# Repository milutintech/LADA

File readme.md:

# LADA
## Interieur
### Mittelkonsole  Kosten ca 500.-
Open Auto Pro
- Waveshare display 
  - https://www.waveshare.com/product/raspberry-pi/displays/lcd-oled/15.6hp-capqled.htm
- PI 4
  - https://www.pi-shop.ch/raspberry-pi-4-model-b-8gb
- CPC200-CCPA (Car Play)
  - https://www.mytrendyphone.ch/shop/carlinkit-cpc200-ccpa-drahtlose-carplay-android-auto-adapter-304415p.html?gclid=CjwKCAiA3aeqBhBzEiwAxFiOBi3R6-FiMQM87529C-vewYi9WbjxqfM-s6FcQSQeUMXNf6h3jQiDPxoCrb8QAvD_BwE
- CSR8510 A10 (Bt)
  -https://www.digitec.ch/de/s1/product/tp-link-ub500-sender-bluetooth-audio-adapter-16644981
- HIFI BERRY
  -https://www.reichelt.com/ch/de/raspberry-pi-shield-beocreate-4-channel-amplifier-rpi-hb-beocreate-p218586.html?PROVID=2808&gclid=CjwKCAiA3aeqBhBzEiwAxFiOBsO-QmUIh61FRokT5aY90-eXIpBP11wS4Q5fO7jmrViyCtoBBXhQuxoC0AgQAvD_BwE
  
### Tacho
Digifitz

## BMS Kosten ca 2700.-
Orion 
### Ansteuerung

### Verkabelung

https://www.orionbms.com/manuals/pdf/orionbms2_wiring_manual.pdf

> - If fewer than 12 cells are populated in a group, unused cell taps must all be connected to the highest
potential cell in that group. For example, if 6 cells are populated in a group, taps 6 – 12 all must be
connected to the positive tap on cell 6.*

> - No cell group may have fewer than 4 cells connected (higher minimums may apply if a cell's
minimum voltage is below 2.8v). If a group of cells ends up with fewer than 4 cells, some cells must
be skipped in one of the other groups and wired into the group with less than 4 to ensure that a
minimum of 4 cells are present.

> - Cell Groups must have a minimum normal working voltage of 11 volts (2.8v per cell for 4 cells) and
an absolute minimum voltage of 10v. Accuracy of voltage measurements is decreased when the
group voltage is below 11 volts.

> - If a cell group has 0 cells connected (the group is skipped entirely), all wires from that group may be
left disconnected.

### Lade und Ready Modi

The BMS has two primary modes of operation: Charge Mode and Ready Mode. The BMS will enter into Charge Mode any time 12 - 24v is applied to the CHARGE power pin (Main I/O pin 3), regardlessof whether READY power is also present or not.

https://www.orionbms.com/manuals/pdf/orionbms2_operational_manual.pdf

> The following functions are enabled (or change) when the BMS is in Charge Mode:
> 1. The charger safety output is allowed to turn on if enabled and if all criteria have been met.
> 2. The BMS will cap the state of charge to the value specified as the "Charged SOC" percentage.
Even if the battery is charged in such a way that would normally cause the SOC to rise above
this value, the value will not exceed the "Charged SOC parameter" while the BMS is in charge
mode.

> 4. When any cell voltage hits the maximum cell voltage (resulting in the BMS turning the charger
off), the BMS will immediately adjust the state of charge to the "Charged SOC" value since the
BMS knows that the battery pack is fully charged at this time.

> 5. The cell balancing algorithm is enabled and will begin balancing as soon as any cell voltage
goes above the "Start Balancing" voltage. Balancing will continue until all cell voltages are
balanced to within the balance delta voltage parameter. See the “How Balancing Works” section
for more information on cell balancing.

> 6. Certain CANBUS messages may be transmitted or not transmitted depending on whether the
BMS is in CHARGE mode or not (if configured).

> 7. The maximum possible current limit for charging is limited to the "Maximum Amperage While
Charging" parameter available on the “Charge Limits” profile settings tab.
> 8. The maximum allowable cell voltage is limited to the "Max. Voltage While Charging" parameter
available on the “Cell Settings” profile settings tab.

### Flussdiagramme Charge und Discharge

charge

discharge

### Offerte BMS

[S07459.pdf](https://github.com/milutintech/LADA/files/13288886/S07459.pdf)

### NLG

### Relais

## Pinout VCU relais

> - Relais 1 Bat arm
> - Relais 2 KühlPumpe
> - Relais 3 Lüfter
> - Relais 4 NLG KL15
> - Relais 5 Rückfahrlicht
> - Relais 6 DMC KL15
> - Relais 7 BSC KL15

## Pinout Input

> - P1/9 RELAY U2
> - P2/22 IGNITION
> - P3/10 UNLCKCON
> - P4/23
> - A0/7 Gaspedal
> - CAN/25 CAN_H
> - CAN/13 CAN_L

## BMS Messages
Source: BMS
ID 0x1 MSB 00 00 00 00 00 00 00 00 LSB 
> - BMS_SOC 0%-100% byte 0
> - BMS_U_BAT 0V-450V byte 1,2
> - BMS_I_BAT 0A-650A byte 3,4
> - BMS_MAX_Discharge 0A-650A 5,6
> - BMS_MAX_Charge 0A-250A 7

## INFO Messages
Source: INFO
ID 0x3 MSB 00 00 00 00 00 00 00 00 LSB 
> - MAX_CHG_SOC 0%-100% byte 0
> - DMC_TrqRq 0Nm-1100Nm byte 1,2
> - NLG_AcCurrLimMax 0A-32A byte 3
> - OFFROAD_MODE 0-1 byte 4

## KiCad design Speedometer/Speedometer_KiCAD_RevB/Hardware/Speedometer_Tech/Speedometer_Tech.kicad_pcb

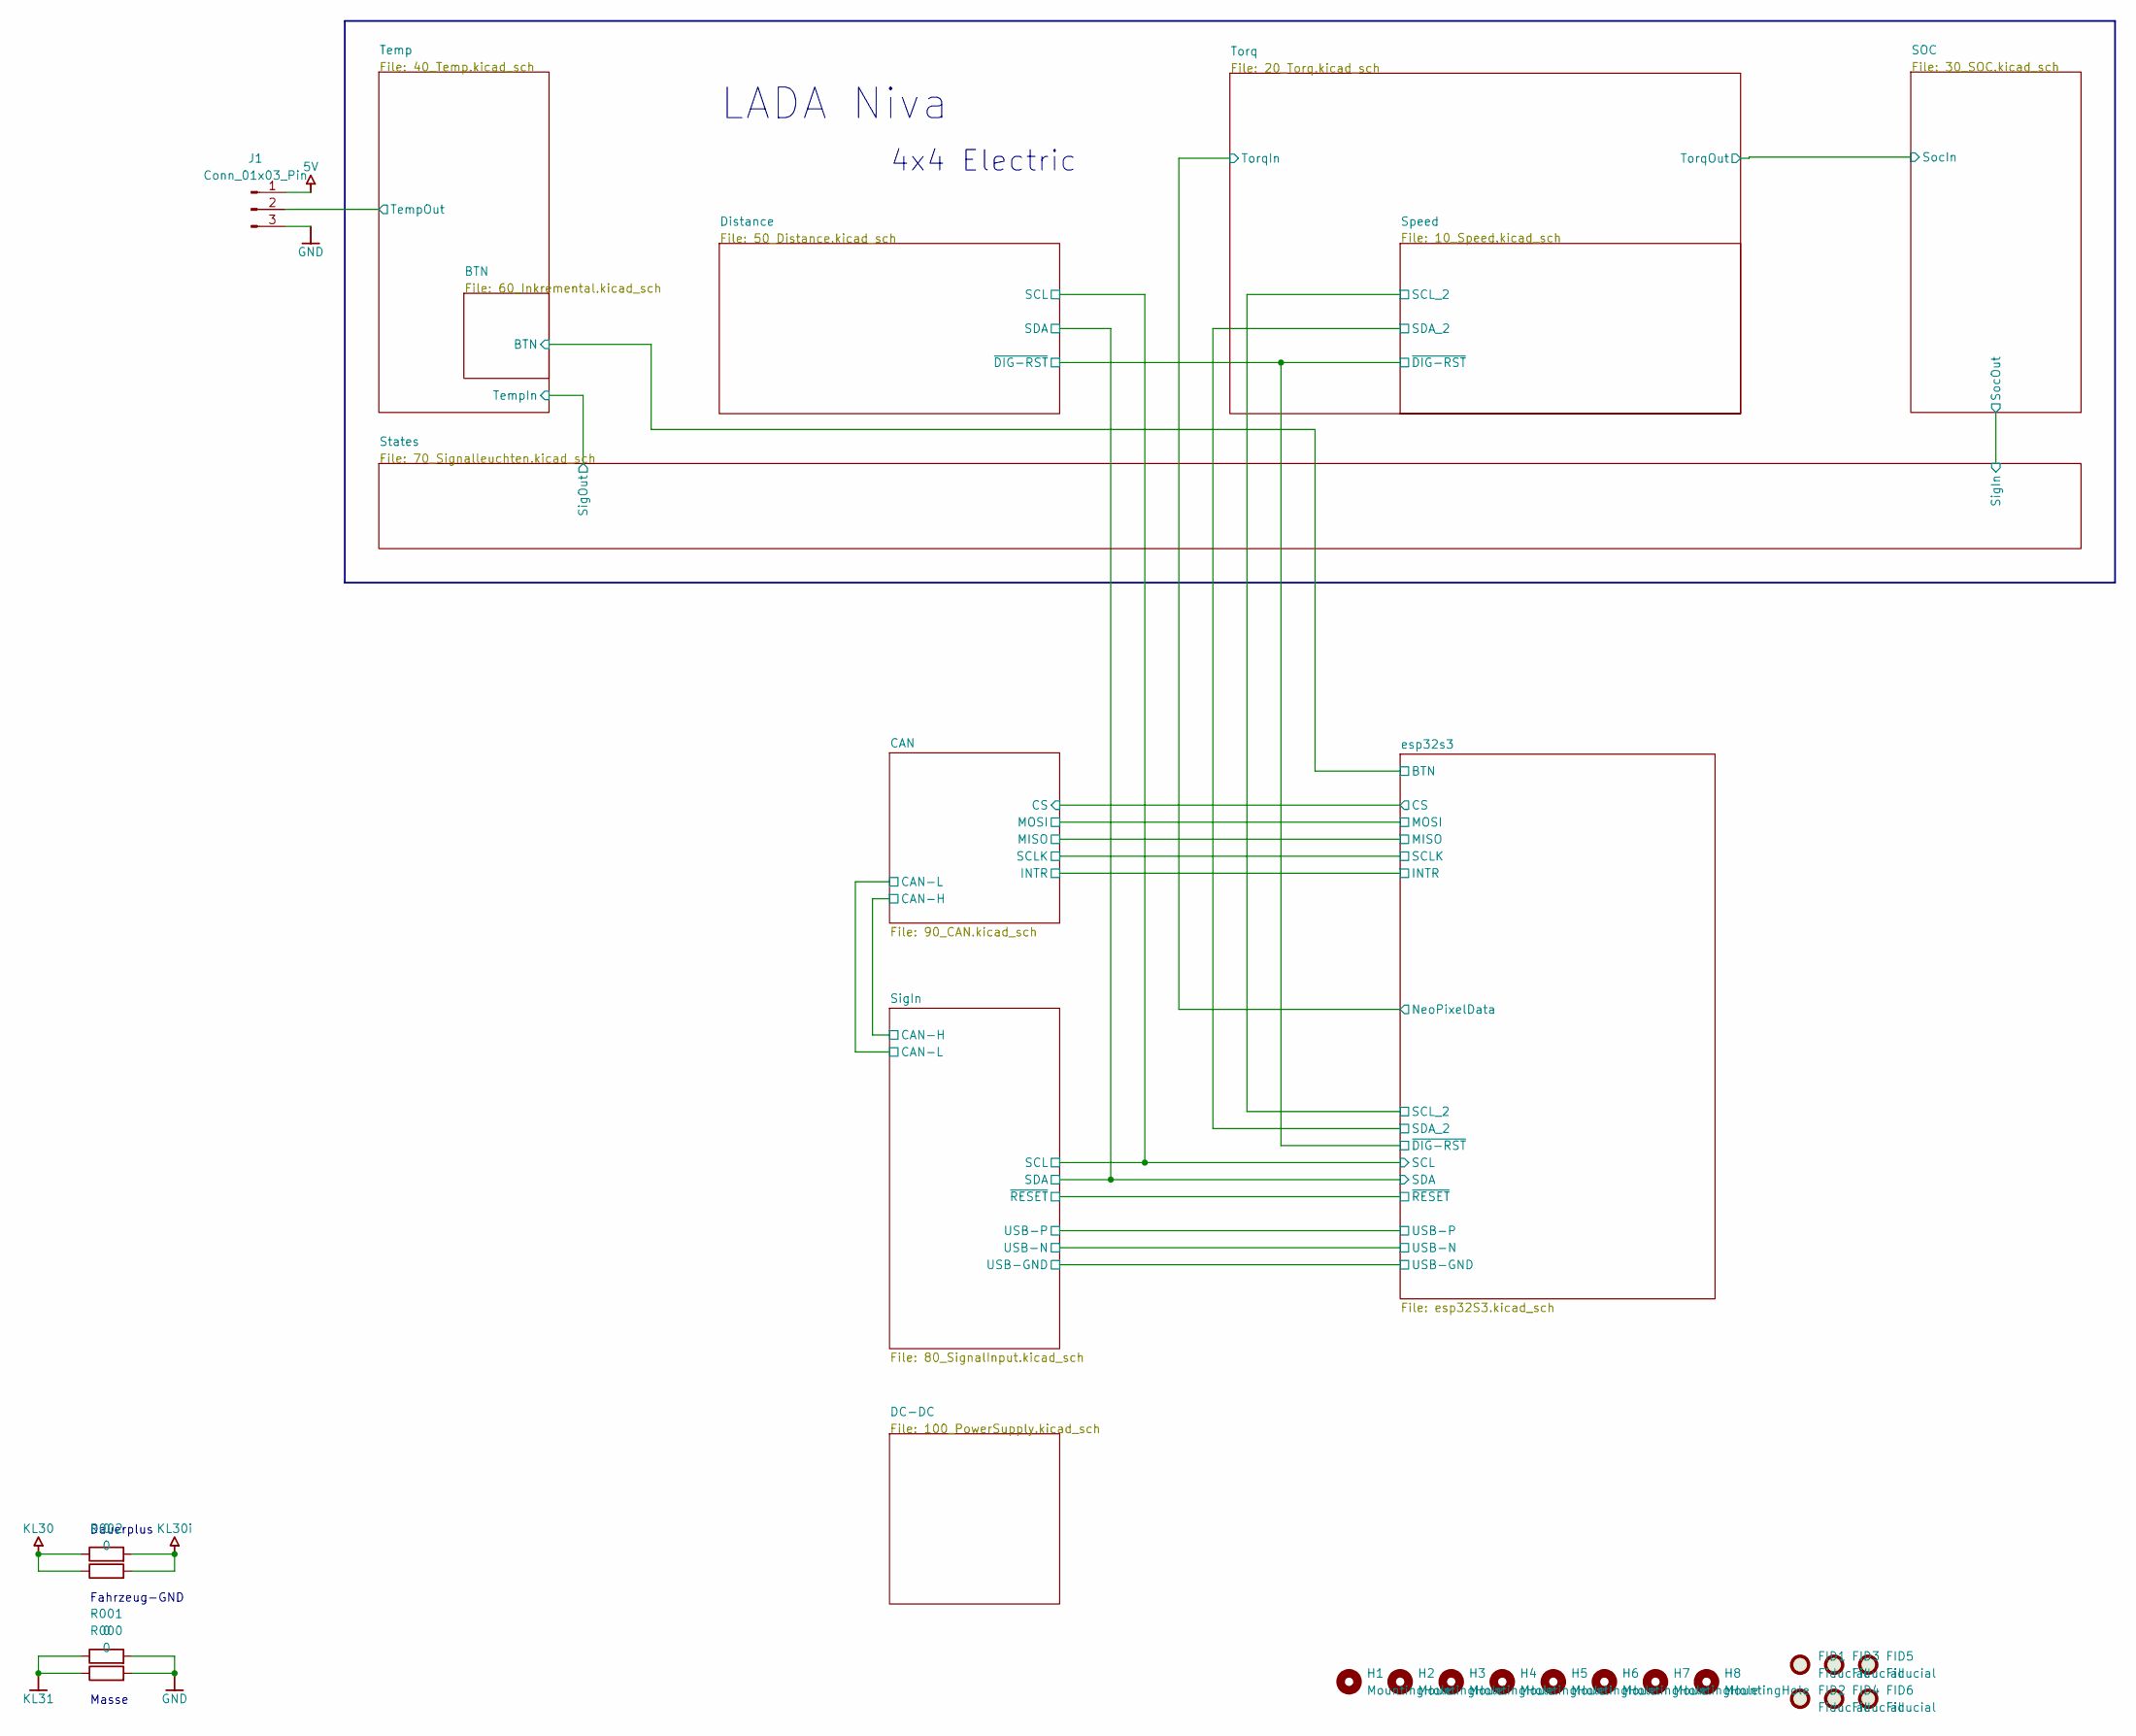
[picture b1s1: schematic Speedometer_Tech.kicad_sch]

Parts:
FID1, FID2, FID3, FID4, FID5, FID6: Fiducial; Fiducial_0.5mm_Mask1mm
H1, H2, H3, H4, H5, H6, H7, H8: MountingHole; MountingHole_4.3mm_M4_ISO7380
J1: Conn_01x03_Pin; PinHeader_1x03_P2.54mm_Horizontal
R000, R001, R002, R003: 0; R_0603_1608Metric

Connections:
5V: J1.1; also elsewhere on the board
/Temp/TempOut: J1.2; also elsewhere on the board
GND: J1.3, R000.2, R001.2; also elsewhere on the board
KL30: R002.1, R003.1; also elsewhere on the board
KL30i: R002.2, R003.2; also elsewhere on the board
KL31: R000.1, R001.1; also elsewhere on the board

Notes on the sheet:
LADA Niva
Masse
4x4 Electric
Dauerplus
Fahrzeug-GND

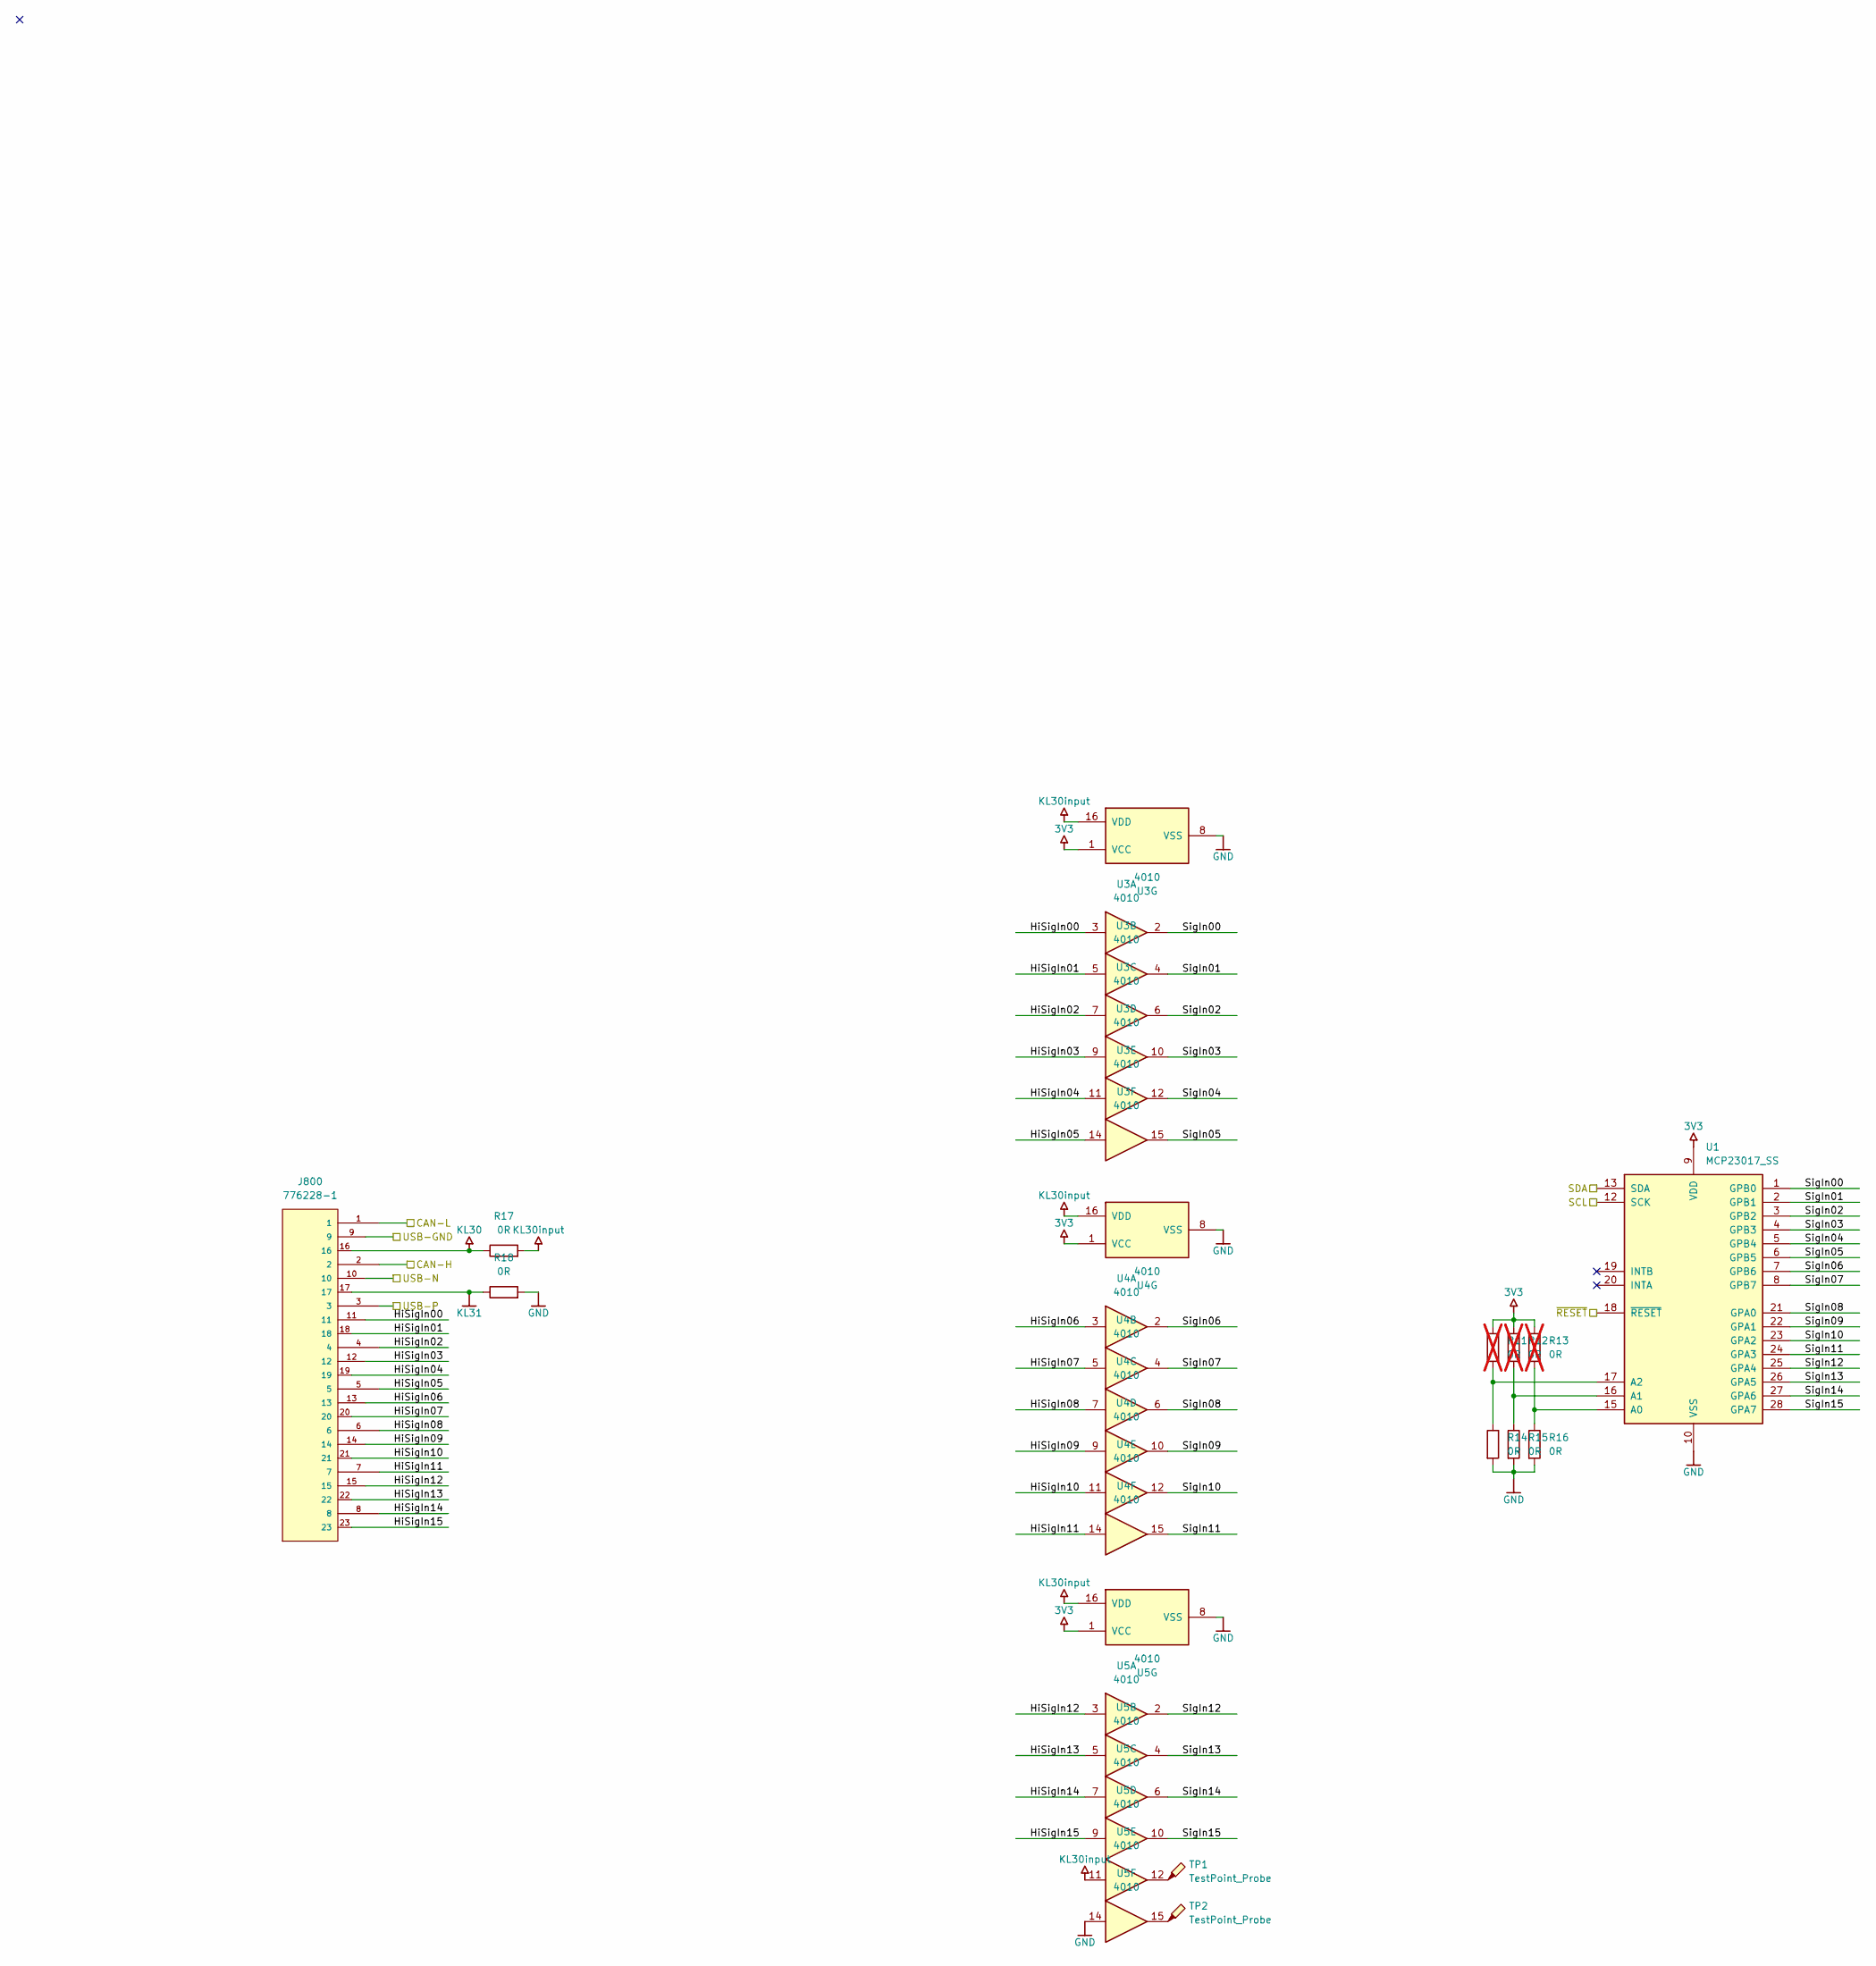
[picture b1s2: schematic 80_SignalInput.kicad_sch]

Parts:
J800: 776228-1; TE_776228-1; PARTREV C13
R11, R12, R13: 0R; R_0603_1608Metric; not fitted
R14, R15, R16, R17, R18: 0R; R_0603_1608Metric
TP1, TP2: TestPoint_Probe; TestPoint_Pad_2.0x2.0mm
U1: MCP23017_SS; SSOP-28_5.3x10.2mm_P0.65mm
U3, U4, U5: 4010; DIP-16_W7.62mm_LongPads

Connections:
3V3: R11.1, R12.1, R13.1, U1.9 (VDD), U3.1 (VCC), U4.1 (VCC), U5.1 (VCC); also elsewhere on the board
/CAN/CAN_H: J800.2; also elsewhere on the board
/CAN/CAN_L: J800.1; also elsewhere on the board
/Distance/SCL: U1.12 (SCK); also elsewhere on the board
/Distance/SDA: U1.13 (SDA); also elsewhere on the board
/SigIn/HiSigIn00: J800.11, U3.3
/SigIn/HiSigIn01: J800.18, U3.5
/SigIn/HiSigIn02: J800.4, U3.7
/SigIn/HiSigIn03: J800.12, U3.9
/SigIn/HiSigIn04: J800.19, U3.11
/SigIn/HiSigIn05: J800.5, U3.14
/SigIn/HiSigIn06: J800.13, U4.3
/SigIn/HiSigIn07: J800.20, U4.5
/SigIn/HiSigIn08: J800.6, U4.7
/SigIn/HiSigIn09: J800.14, U4.9
/SigIn/HiSigIn10: J800.21, U4.11
/SigIn/HiSigIn11: J800.7, U4.14
/SigIn/HiSigIn12: J800.15, U5.3
/SigIn/HiSigIn13: J800.22, U5.5
/SigIn/HiSigIn14: J800.8, U5.7
/SigIn/HiSigIn15: J800.23, U5.9
/SigIn/SigIn00: U1.1 (GPB0), U3.2
/SigIn/SigIn01: U1.2 (GPB1), U3.4
/SigIn/SigIn02: U1.3 (GPB2), U3.6
/SigIn/SigIn03: U1.4 (GPB3), U3.10
/SigIn/SigIn04: U1.5 (GPB4), U3.12
/SigIn/SigIn05: U1.6 (GPB5), U3.15
/SigIn/SigIn06: U1.7 (GPB6), U4.2
/SigIn/SigIn07: U1.8 (GPB7), U4.4
/SigIn/SigIn08: U1.21 (GPA0), U4.6
/SigIn/SigIn09: U1.22 (GPA1), U4.10
/SigIn/SigIn10: U1.23 (GPA2), U4.12
/SigIn/SigIn11: U1.24 (GPA3), U4.15
/SigIn/SigIn12: U1.25 (GPA4), U5.2
/SigIn/SigIn13: U1.26 (GPA5), U5.4
/SigIn/SigIn14: U1.27 (GPA6), U5.6
/SigIn/SigIn15: U1.28 (GPA7), U5.10
/SigIn/USB-N: J800.10; also elsewhere on the board
/SigIn/USB-P: J800.3; also elsewhere on the board
/SigIn/~RESET: U1.18 (~RESET); also elsewhere on the board
GND: J800.9, R14.2, R15.2, R16.2, R18.2, U1.10 (VSS), U3.8 (VSS), U4.8 (VSS), U5.8 (VSS), U5.14; also elsewhere on the board
KL30: J800.16, R17.1; also elsewhere on the board
KL30input: R17.2, U3.16 (VDD), U4.16 (VDD), U5.11, U5.16 (VDD)
KL31: J800.17, R18.1; also elsewhere on the board
unnamed: TP1.1, U5.12
unnamed: TP2.1, U5.15
unnamed: R13.2, R16.1, U1.15 (A0)
unnamed: R12.2, R15.1, U1.16 (A1)
unnamed: R11.2, R14.1, U1.17 (A2)

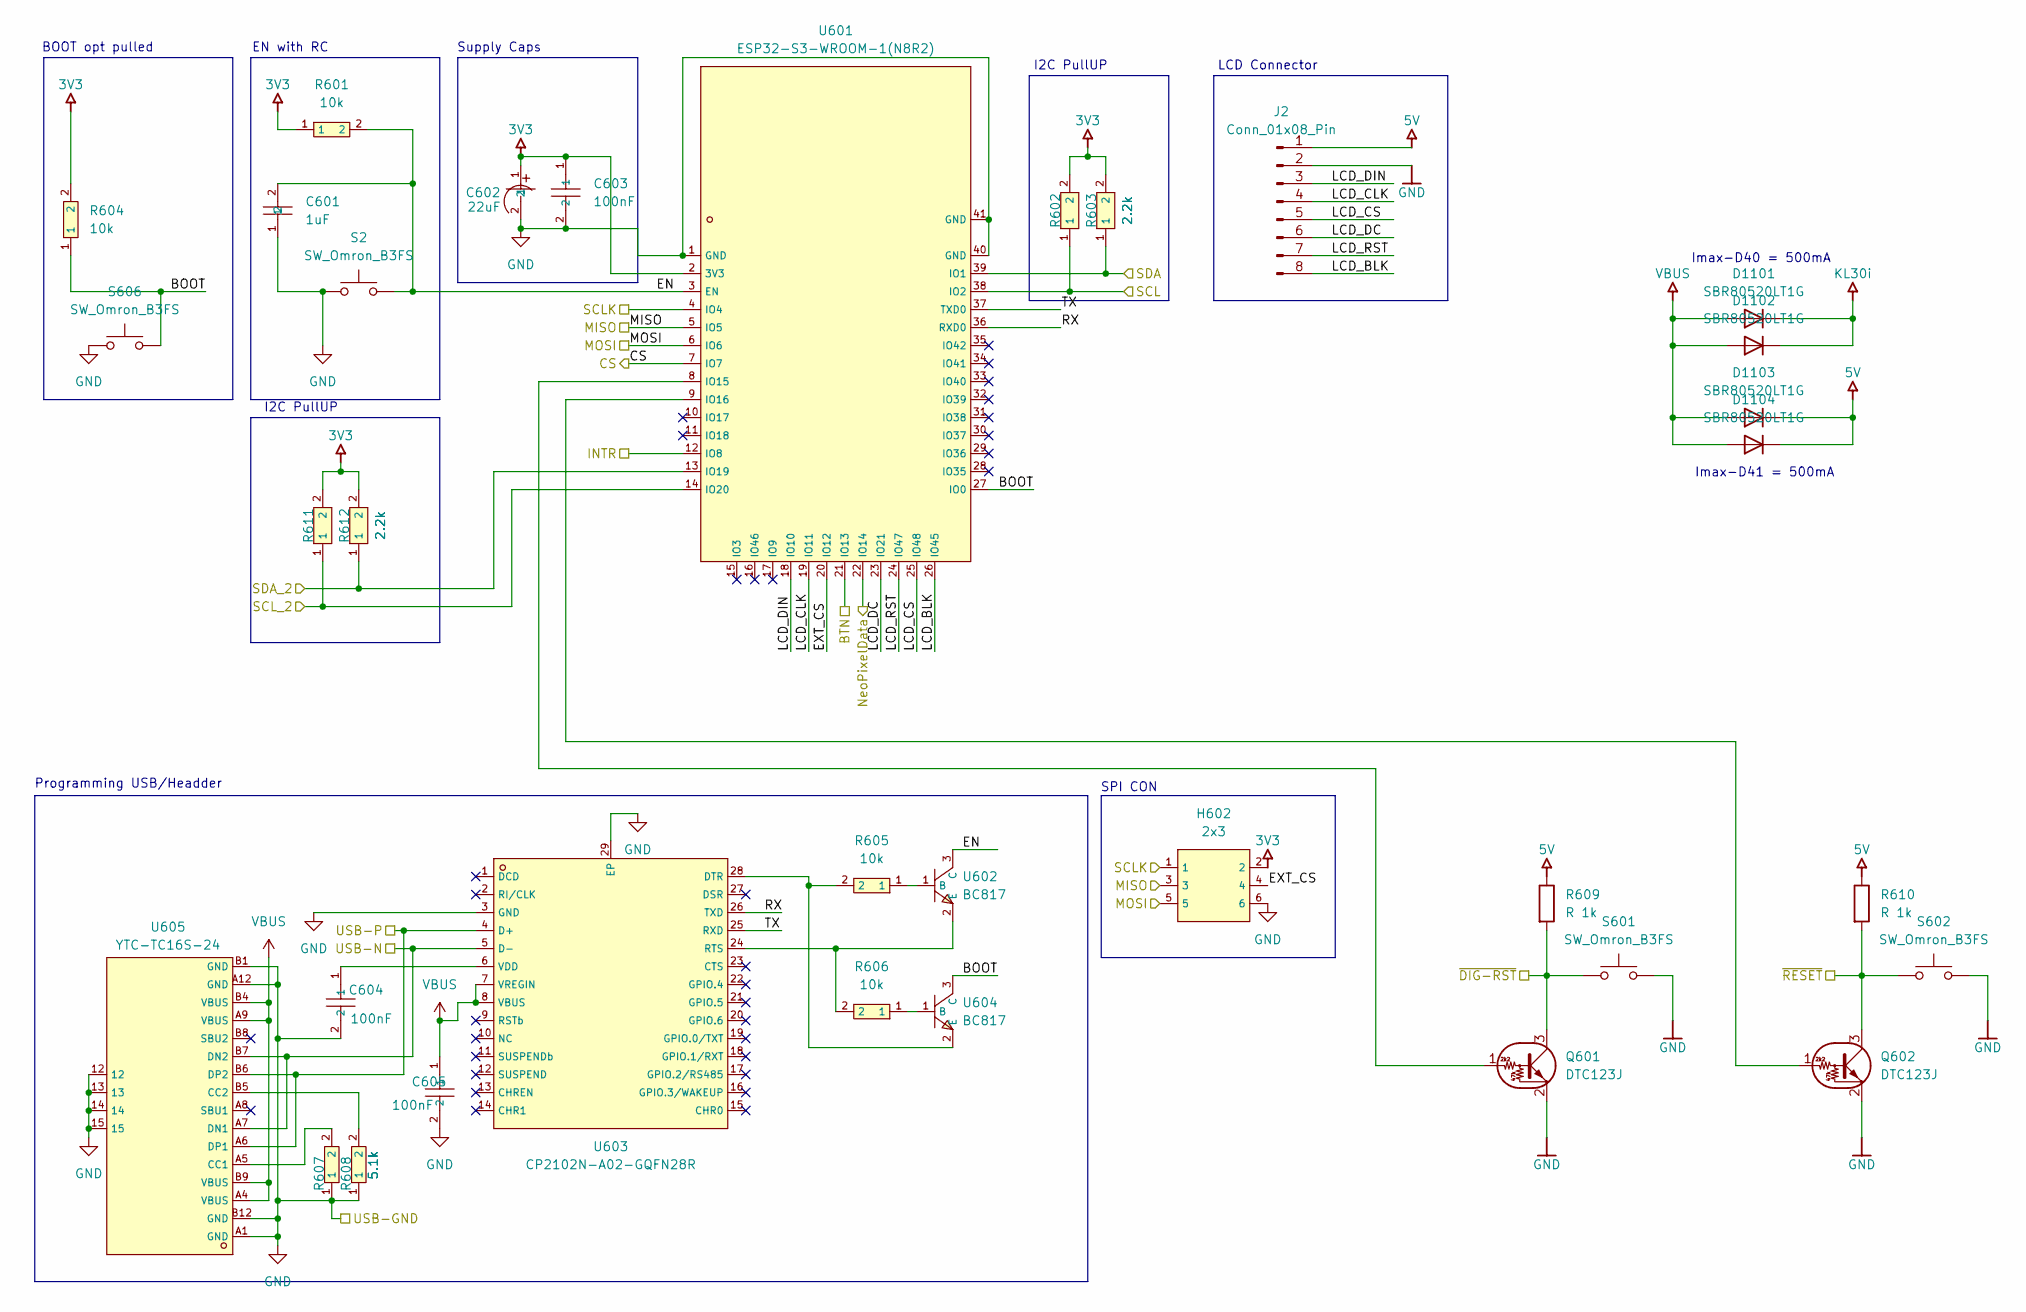
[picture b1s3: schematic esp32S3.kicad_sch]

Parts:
C601: 1uF; C_0805_2012Metric; LCSC C28323
C602: 22uF; C_0805_2012Metric; LCSC C131114
C603: 100nF; C_0201_0603Metric; LCSC C14663
C604: 100nF; C_0603_1608Metric; LCSC C14663
C605: 100nF; R_0603_1608Metric; LCSC C14663
D1101, D1102, D1103, D1104: SBR80520LT1G; D_SOD-123
H602: 2x3; PinHeader_2x03_P2.54mm_Vertical_SMD; LCSC C65114
J2: Conn_01x08_Pin; Harwin_M20-89008xx_1x08_P2.54mm_Horizontal
Q601, Q602: DTC123J; SOT-23
R601, R604, R605, R606: 10k; R_0603_1608Metric; LCSC C98220
R602, R603, R611, R612: 2.2k; R_0603_1608Metric; LCSC C227479
R607, R608: 5.1k; R_0603_1608Metric; LCSC C186203
R609, R610: R 1k; R_0603_1608Metric
S2, S601, S602, S606: SW_Omron_B3FS; SW_SPST_Omron_B3FS-100xP
U601: ESP32-S3-WROOM-1(N8R2); ESP32-S3-WROOM-2; LCSC C2913204
U602, U604: BC817; SOT-23-3; LCSC C549442
U603: CP2102N-A02-GQFN28R; VQFN-28-1EP_5x5mm_P0.5mm_EP3.25x3.25mm; LCSC C964632
U605: YTC-TC16S-24; TYPEC-300D-BCP16H100; LCSC C2927291

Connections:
3V3: C602.1, C603.1, H602.2, R601.1, R602.2, R603.2, R604.2, R611.2, R612.2, U601.2 (3V3); also elsewhere on the board
5V: D1103.1 (K), D1104.1 (K), J2.1, R609.1, R610.1; also elsewhere on the board
/BTN/BTN: U601.21 (IO13); also elsewhere on the board
/CAN/INTR: U601.12 (IO8); also elsewhere on the board
/CAN/SCLK: H602.1, U601.4 (IO4); also elsewhere on the board
/Distance/SCL: R602.1, U601.38 (IO2); also elsewhere on the board
/Distance/SDA: R603.1, U601.39 (IO1); also elsewhere on the board
/Distance/~DIG-RST: Q601.3 (C), R609.2, S601.1; also elsewhere on the board
/SigIn/USB-N: U603.5 (D-), U605.A7 (DN1), U605.B7 (DN2); also elsewhere on the board
/SigIn/USB-P: U603.4 (D+), U605.A6 (DP1), U605.B6 (DP2); also elsewhere on the board
/SigIn/~RESET: Q602.3 (C), R610.2, S602.1; also elsewhere on the board
/Speed/SCL_2: R611.1, U601.14 (IO20); also elsewhere on the board
/Speed/SDA_2: R612.1, U601.13 (IO19); also elsewhere on the board
/Torq/TorqIn: U601.22 (IO14); also elsewhere on the board
/esp32s3/BOOT: R604.1, S606.2, U601.27 (IO0), U604.3 (C)
/esp32s3/CS: U601.7 (IO7); also elsewhere on the board
/esp32s3/EN: C601.2, R601.2, S2.2, U601.3 (EN), U602.3 (C)
/esp32s3/EXT_CS: H602.4, U601.20 (IO12)
/esp32s3/LCD_BLK: J2.8, U601.26 (IO45)
/esp32s3/LCD_CLK: J2.4, U601.19 (IO11)
/esp32s3/LCD_CS: J2.5, U601.25 (IO48)
/esp32s3/LCD_DC: J2.6, U601.23 (IO21)
/esp32s3/LCD_DIN: J2.3, U601.18 (IO10)
/esp32s3/LCD_RST: J2.7, U601.24 (IO47)
/esp32s3/MISO: H602.3, U601.5 (IO5); also elsewhere on the board
/esp32s3/MOSI: H602.5, U601.6 (IO6); also elsewhere on the board
/esp32s3/RX: U601.36 (RXD0), U603.26 (TXD)
/esp32s3/TX: U601.37 (TXD0), U603.25 (RXD)
GND: C601.1, C602.2, C603.2, C604.2, C605.2, H602.6, J2.2, Q601.2 (E), Q602.2 (E), R607.1, R608.1, S2.1, S601.2, S602.2, S606.1, U601.1 (GND), U601.40 (GND), U601.41 (GND), U603.3 (GND), U603.29 (EP), U605.12, U605.13, U605.14, U605.15, U605.A1 (GND), U605.A12 (GND), U605.B1 (GND), U605.B12 (GND); also elsewhere on the board
KL30i: D1101.1 (K), D1102.1 (K); also elsewhere on the board
unnamed: Q601.1 (B), U601.8 (IO15)
unnamed: Q602.1 (B), U601.9 (IO16)
unnamed: R605.1, U602.1 (B)
unnamed: R606.2, U602.2 (E), U603.24 (RTS)
unnamed: R605.2, U603.28 (DTR), U604.2 (E)
unnamed: C604.1, U603.6 (VDD)
unnamed: R606.1, U604.1 (B)
unnamed: R607.2, U605.A5 (CC1)
unnamed: R608.2, U605.B5 (CC2)
VBUS: C605.1, D1101.2 (A), D1102.2 (A), D1103.2 (A), D1104.2 (A), U603.7 (VREGIN), U603.8 (VBUS), U605.A4 (VBUS), U605.A9 (VBUS), U605.B4 (VBUS), U605.B9 (VBUS)

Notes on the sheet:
EN with RC
Programming USB/Headder
I2C PullUP
Supply Caps
LCD Connector
Imax-D41 = 500mA
SPI CON
BOOT opt pulled
Imax-D40 = 500mA

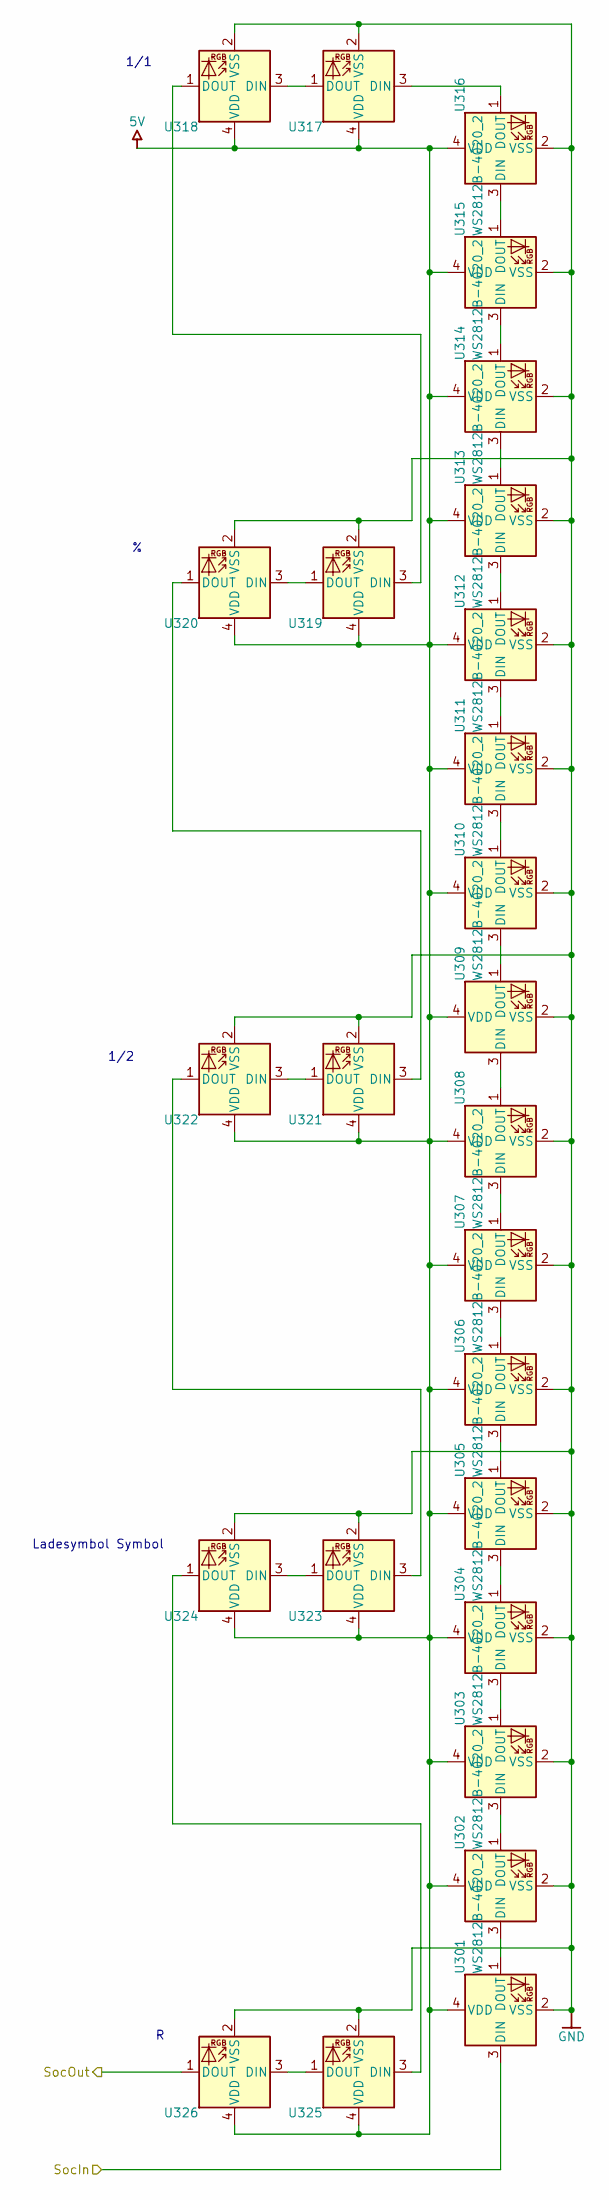
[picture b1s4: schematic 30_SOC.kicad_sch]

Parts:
U301, U302, U303, U304, U305, U306, U307, U308, U309, U310, U311, U312, U313, U314, U315, U316, U317, U318, U319, U320, U321, U322, U323, U324, U325, U326: WS2812B-4020_2; LED_WS2812B-2020_PLCC4_2.0x2.0mm

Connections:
5V: U301.4 (VDD), U302.4 (VDD), U303.4 (VDD), U304.4 (VDD), U305.4 (VDD), U306.4 (VDD), U307.4 (VDD), U308.4 (VDD), U309.4 (VDD), U310.4 (VDD), U311.4 (VDD), U312.4 (VDD), U313.4 (VDD), U314.4 (VDD), U315.4 (VDD), U316.4 (VDD), U317.4 (VDD), U318.4 (VDD), U319.4 (VDD), U320.4 (VDD), U321.4 (VDD), U322.4 (VDD), U323.4 (VDD), U324.4 (VDD), U325.4 (VDD), U326.4 (VDD); also elsewhere on the board
/SOC/SocIn: U301.3 (DIN); also elsewhere on the board
/SOC/SocOut: U326.1 (DOUT); also elsewhere on the board
GND: U301.2 (VSS), U302.2 (VSS), U303.2 (VSS), U304.2 (VSS), U305.2 (VSS), U306.2 (VSS), U307.2 (VSS), U308.2 (VSS), U309.2 (VSS), U310.2 (VSS), U311.2 (VSS), U312.2 (VSS), U313.2 (VSS), U314.2 (VSS), U315.2 (VSS), U316.2 (VSS), U317.2 (VSS), U318.2 (VSS), U319.2 (VSS), U320.2 (VSS), U321.2 (VSS), U322.2 (VSS), U323.2 (VSS), U324.2 (VSS), U325.2 (VSS), U326.2 (VSS); also elsewhere on the board
unnamed: U301.1 (DOUT), U302.3 (DIN)
unnamed: U302.1 (DOUT), U303.3 (DIN)
unnamed: U303.1 (DOUT), U304.3 (DIN)
unnamed: U304.1 (DOUT), U305.3 (DIN)
unnamed: U305.1 (DOUT), U306.3 (DIN)
unnamed: U306.1 (DOUT), U307.3 (DIN)
unnamed: U307.1 (DOUT), U308.3 (DIN)
unnamed: U308.1 (DOUT), U309.3 (DIN)
unnamed: U309.1 (DOUT), U310.3 (DIN)
unnamed: U310.1 (DOUT), U311.3 (DIN)
unnamed: U311.1 (DOUT), U312.3 (DIN)
unnamed: U312.1 (DOUT), U313.3 (DIN)
unnamed: U313.1 (DOUT), U314.3 (DIN)
unnamed: U314.1 (DOUT), U315.3 (DIN)
unnamed: U315.1 (DOUT), U316.3 (DIN)
unnamed: U316.1 (DOUT), U317.3 (DIN)
unnamed: U317.1 (DOUT), U318.3 (DIN)
unnamed: U318.1 (DOUT), U319.3 (DIN)
unnamed: U319.1 (DOUT), U320.3 (DIN)
unnamed: U320.1 (DOUT), U321.3 (DIN)
unnamed: U321.1 (DOUT), U322.3 (DIN)
unnamed: U322.1 (DOUT), U323.3 (DIN)
unnamed: U323.1 (DOUT), U324.3 (DIN)
unnamed: U324.1 (DOUT), U325.3 (DIN)
unnamed: U325.1 (DOUT), U326.3 (DIN)

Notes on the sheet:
1/2
1/1
Ladesymbol Symbol

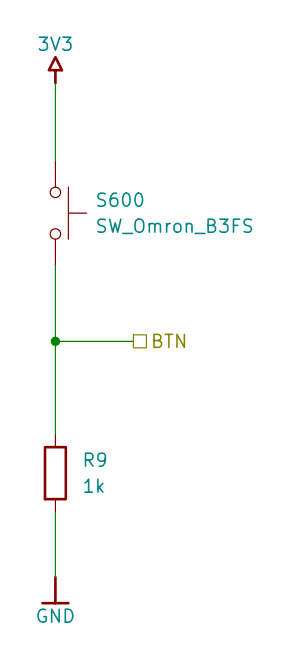
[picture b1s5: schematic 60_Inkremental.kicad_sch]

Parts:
R9: 1k; R_0603_1608Metric
S600: SW_Omron_B3FS; SW_SPST_Omron_B3FS-100xP

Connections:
3V3: S600.1; also elsewhere on the board
/BTN/BTN: R9.1, S600.2; also elsewhere on the board
GND: R9.2; also elsewhere on the board
